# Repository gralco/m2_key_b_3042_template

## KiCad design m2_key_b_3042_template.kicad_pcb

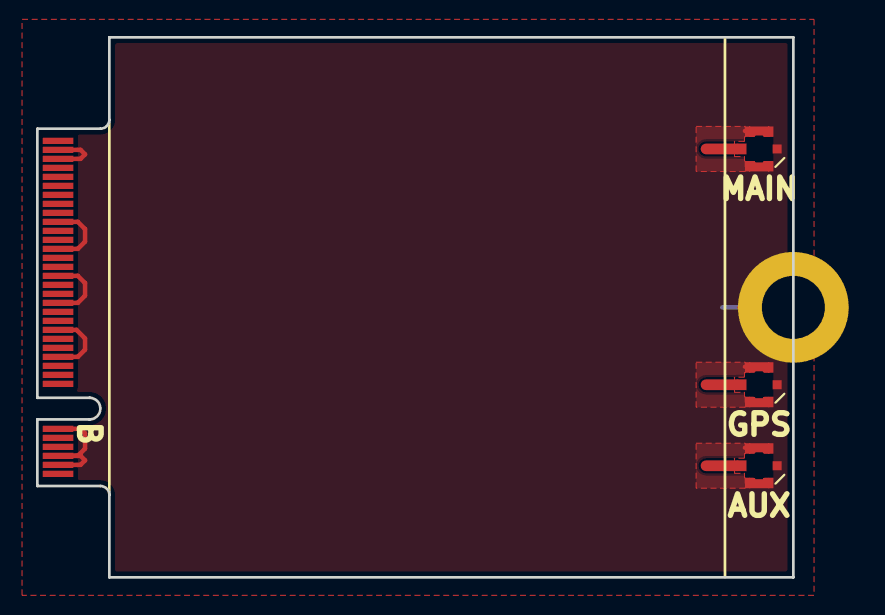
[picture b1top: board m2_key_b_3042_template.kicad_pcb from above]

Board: 2 copper layers, 42.0 x 30.0 mm, 4 parts (0 on the bottom side), 2 nets.

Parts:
ANT1, ANT2, ANT4: Conn_Coaxial; MHF4_20449-001E
J1: M.2_Key_B; M.2_Key_B_Gold_Fingers

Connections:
+3V3: J1.2, J1.4, J1.70, J1.72, J1.74
GND: ANT1.2, ANT2.2, ANT4.2, J1.3, J1.5, J1.11, J1.27, J1.33, J1.39, J1.45, J1.51, J1.57, J1.71, J1.73

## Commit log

2024-05-11 Include MHF4 coax connectors for the baseband, diversity, and GNSS antennae
    Improved the soldermask and mounting hole.
    Included silkscreen designating the component area.
    Antennae MHF4 coax connectors show what orientation they need to be placed in (chamfer).
2024-05-11 Add all project files
2024-05-11 Plot schematic to PDF and included title block info
2024-05-11 Add MHF4 datasheet to the field values and remove the text reference
2024-05-11 Fix unconnected ground nets on MHF4 connectors.
    DRC no longer complains about the polygon shaped GND pads of the MHF4 footprints.
2024-05-11 Include antennae track transmission line impedance calculations which are as close as possible to the expected true value.
    Using the MHF4 recommended 0.6mm track width and 0.12mm space for the 50Ohm CPW.
    Used 4PCB's FR406 relative permitivity and dielectric loss factor values.
    Used slightly less ideal values for the various constants.
2024-05-11 Add coplanar waveguide calculations for the MHF4 antennae tracks
2024-05-11 Include copper zones which control the 50Ohm coplanar waveguide for the antennae.
2024-05-11 Work around KiCad Bug #1460787 by making ground filled zones located at the CPW for the antennae the same priority level (0).
    Changing any value in thes "encapsulated" filled zones will cause them to disappear!!!
    Currently DRC is not complaining but it may later on with certain edits.
2024-05-11 Include smaller custom 0.508mm diameter 0.254mm drill sized via
2024-05-11 Add note about signal integrity for routing
2024-05-11 Update the outer filled zone parameters to be closer to the default whilst still giving the recommended 0.25mm clearance away from the gold finger connector.
2024-05-11 Reduce the area of the no-fill zone keeping the bottom ground pour from getting close to the gold finger connector on either edge of the board.

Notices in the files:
m2_key_b_3042_template.kicad_pcb:
Copyright 2018
